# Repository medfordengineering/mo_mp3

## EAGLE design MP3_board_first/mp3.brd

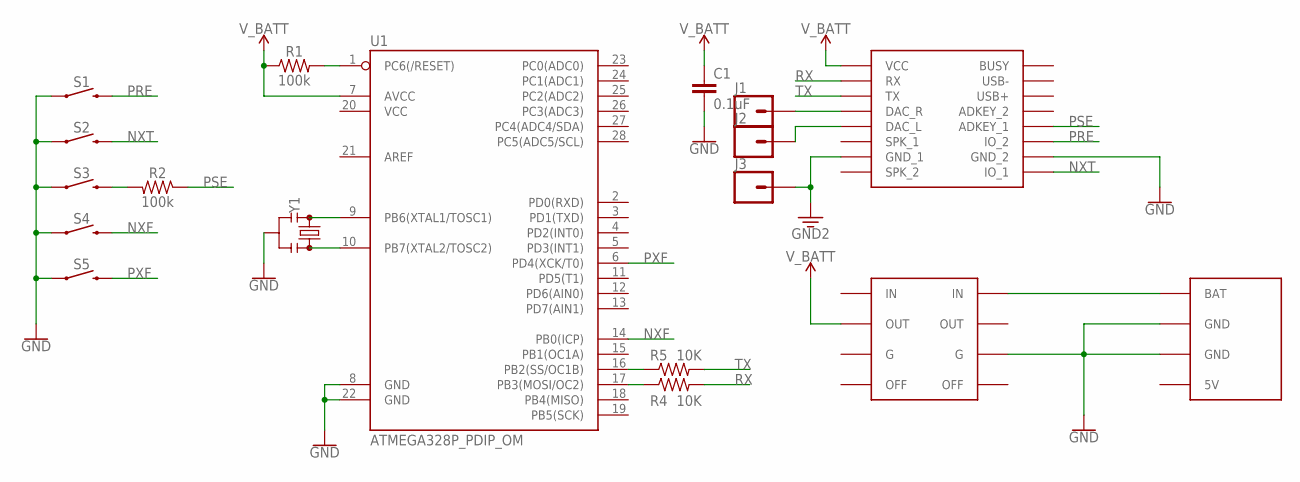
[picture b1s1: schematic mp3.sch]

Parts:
C1: 0.1uF; CAP-PTH-SMALL-KIT
J1, J2, J3: CONN_01PTH_NO_SILK_KIT; 1X01NS_KIT
R1, R2: 100k; AXIAL-0.3
R4, R5: 10K; AXIAL-0.3
S1, S2, S3, S4, S5: MOMENTARY-SWITCH-SPST-PTH-RIGHT-ANGLE; TACTILE_SWITCH_PTH_RIGHT_ANGLE
U1: ATMEGA328P_PDIP_OM; DIP28_OMILL
U$1: DFPLAYER
U$2: ADAFRUIT_SOFTPOWER
U$3: ADAFRUIT_CHARGER
Y1: RESONATOROM; RESONATOR-PTH-7.6X3.3-OM

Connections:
3.3V: J3.1, U$1.GND_1
GND: C1.2, S1.1, S2.1, S3.1, S4.1, S5.1, U1.8 (GND), U1.22 (GND), U$1.GND_2, U$2.P$2 (G), U$3.P$2 (GND), U$3.P$3 (GND), Y1.2
unnamed: U1.9 (PB6(XTAL1/TOSC1)), Y1.1
unnamed: U1.10 (PB7(XTAL2/TOSC2)), Y1.3
unnamed: R1.P$2 (2), U1.1 (PC6(/RESET))
unnamed: R5.P$1 (1), U1.17 (PB3(MOSI/OC2))
unnamed: R4.P$1 (1), U1.16 (PB2(SS/OC1B))
unnamed: R2.P$2 (2), S3.2
unnamed: U$2.P$4 (IN), U$3.P$1 (BAT)
unnamed: J1.1, U$1.DAC_R
unnamed: J2.1, U$1.DAC_L
NXF: S4.2, U1.14 (PB0(ICP))
NXT: S2.2, U$1.IO1 (IO_1)
PRE: S1.2, U$1.IO2 (IO_2)
PSE: R2.P$1 (1), U$1.ADKEY1 (ADKEY_1)
PXF: S5.2, U1.6 (PD4(XCK/T0))
RX: R5.P$2 (2), U$1.RX
TX: R4.P$2 (2), U$1.TX
V_BATT: C1.1, R1.P$1 (1), U1.7 (AVCC), U$1.VCC, U$2.P$6 (OUT)

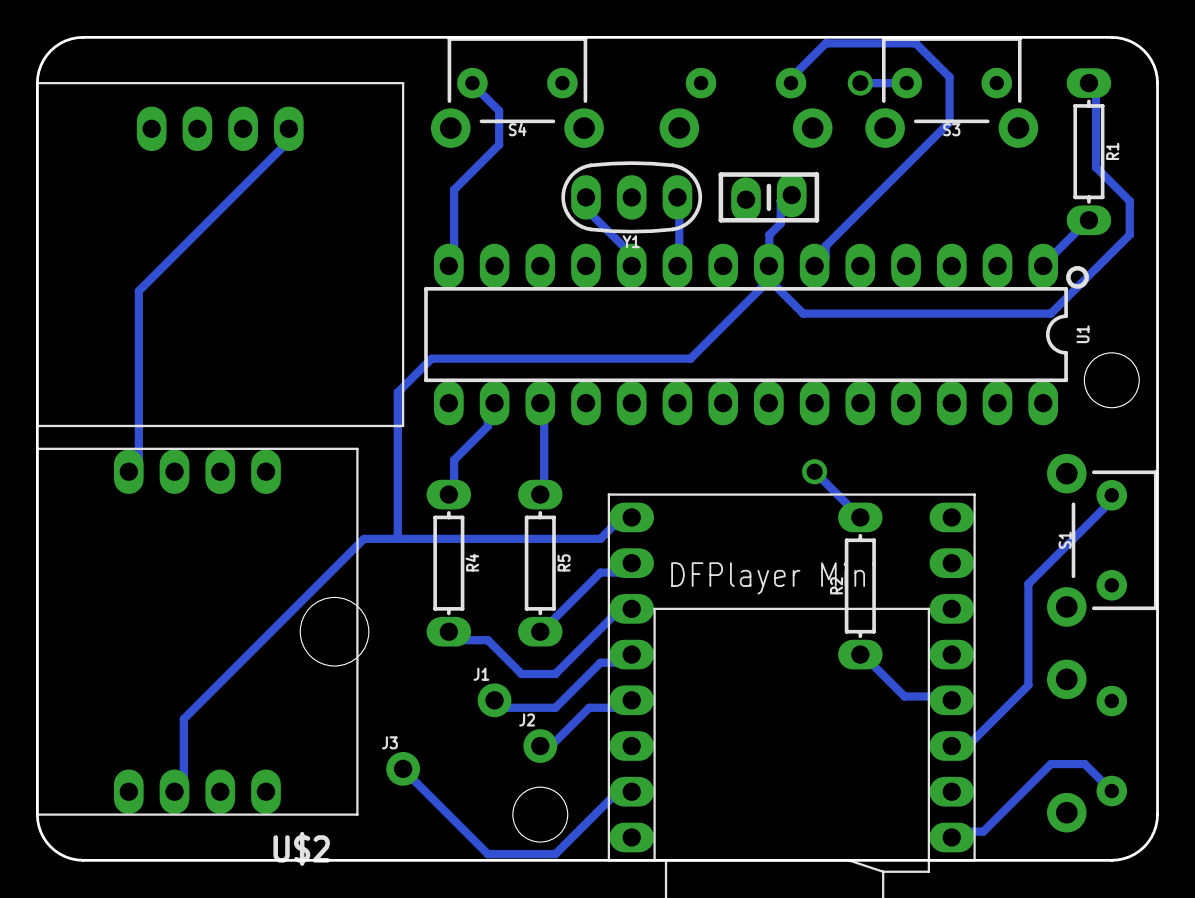
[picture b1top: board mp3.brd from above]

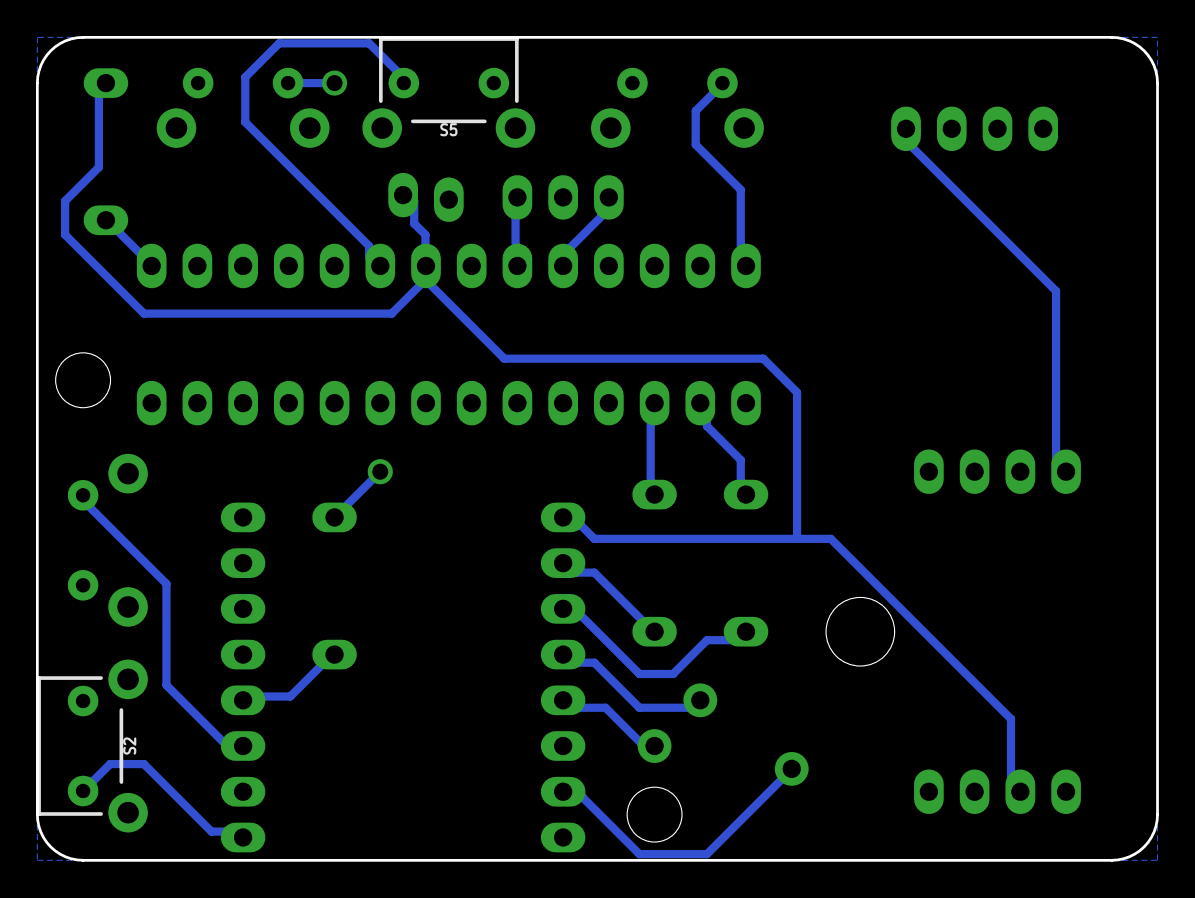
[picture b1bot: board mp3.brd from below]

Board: 2 copper layers, 62.2 x 45.7 mm, 18 parts (2 on the bottom side), 19 nets.

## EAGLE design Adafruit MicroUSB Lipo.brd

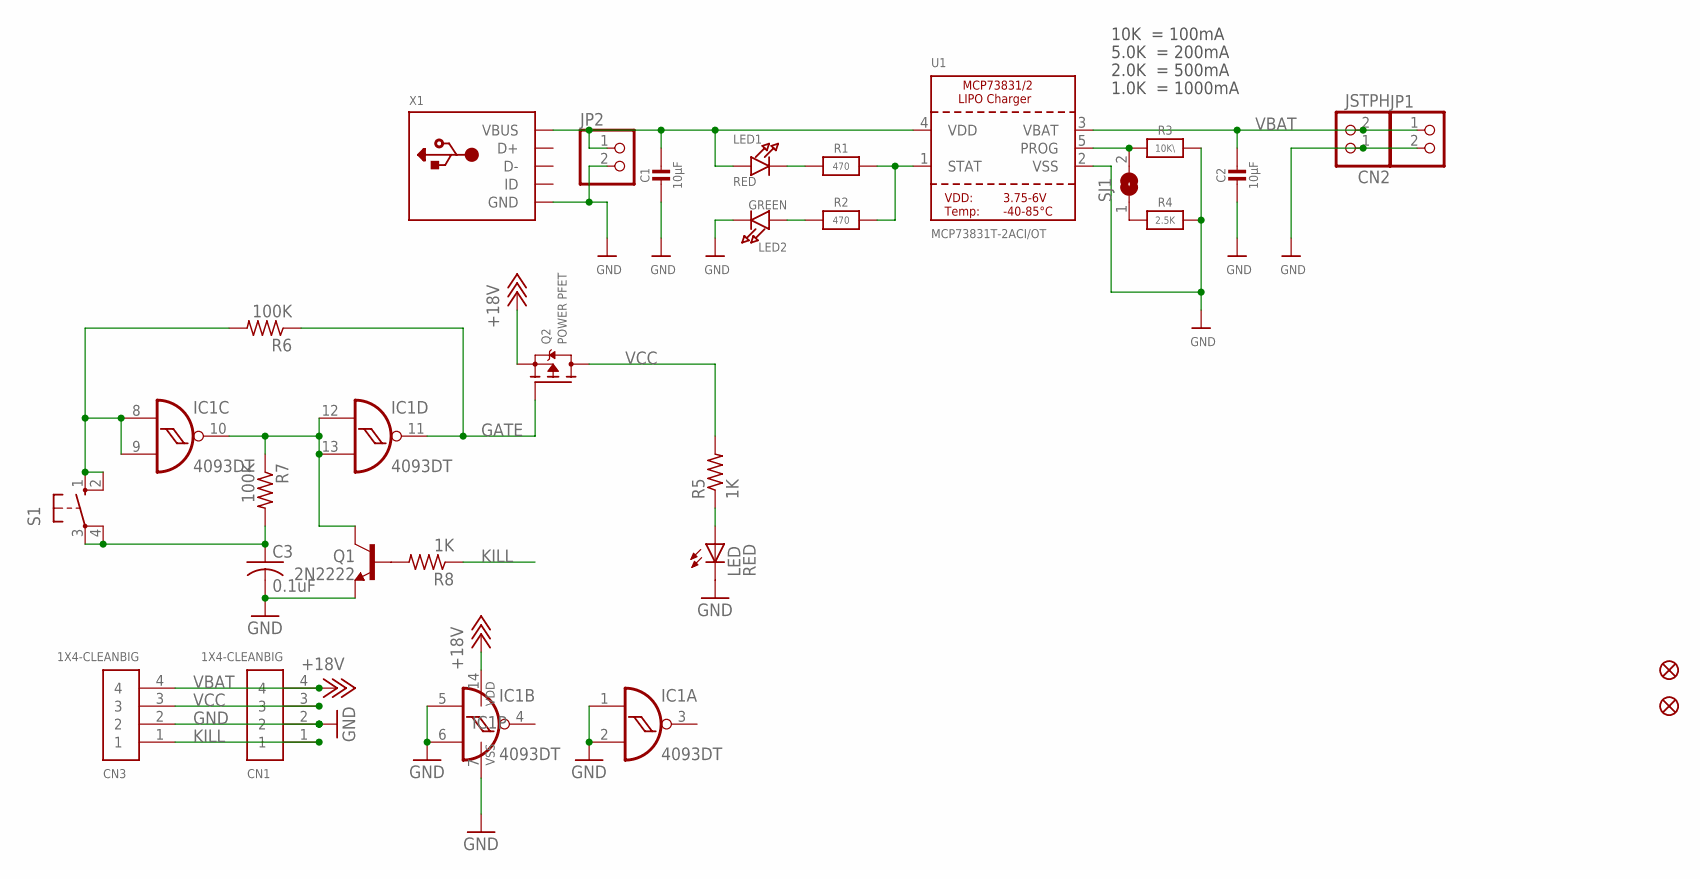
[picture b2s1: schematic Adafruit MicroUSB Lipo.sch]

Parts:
C1, C2: 10µF; 0805-NO
C3: 0.1uF; C0805
CN1, CN3: 1X4-CLEANBIG; 1X04-CLEANBIG
CN2: JSTPH; JSTPH2
FID1, FID2: FIDUCIAL""; FIDUCIAL_1MM
IC1: 4093DT; MC14093B-TSSOP14
JP1, JP2: HEADER-1X2ROUND; 1X02_ROUND
LED: RED; CHIP-LED0805
LED1: RED; CHIPLED_0805_NOOUTLINE
LED2: GREEN; CHIPLED_0805_NOOUTLINE
Q1: 2N2222; SOT23-BEC
Q2: POWER PFET; SOT23-WIDE
R1, R2: 470; 0805-NO
R3: 10K\; 0805-NO
R4: 2.5K; 0805-NO
R5, R8: 1K; R0805
R6, R7: 100K; R0805
S1: 40-XX-ROUND; B3F-40XX-ROUND
SJ1: SOLDERJUMPER; SOLDERJUMPER_ARROW_NOPASTE
U1: MCP73831T-2ACI/OT; SOT23-5
X1: USBMICRO_20329; 4UCONN_20329

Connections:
GATE: IC1.11 (O), Q2.1 (G), R6.1
GND: C1.2, C2.2, C3.2, CN1.2, CN2.1, CN3.2, IC1.1 (I0), IC1.2 (I1), IC1.5 (I0), IC1.6 (I1), IC1.7 (VSS), JP1.2, JP2.2, LED.C, LED2.C, Q1.E, R3.2, R4.2, U1.2 (VSS), X1.BASE@1 (GND), X1.BASE@2 (GND), X1.GND, X1.SPRT@1 (GND), X1.SPRT@2 (GND), X1.SPRT@3 (GND), X1.SPRT@4 (GND)
KILL: CN1.1, CN3.1, R8.1
unnamed: LED1.C, R1.1
unnamed: R1.2, R2.2, U1.1 (STAT)
unnamed: R4.1, SJ1.1
unnamed: IC1.10 (O), IC1.12 (I0), IC1.13 (I1), Q1.C, R7.1
unnamed: R3.1, SJ1.2, U1.5 (PROG)
unnamed: LED2.A, R2.1
unnamed: LED.A, R5.1
unnamed: C3.1, R7.2, S1.3, S1.4 (P1)
unnamed: IC1.8 (I0), IC1.9 (I1), R6.2, S1.1 (S), S1.2 (S1)
unnamed: Q1.B, R8.2
VBAT: C2.1, CN1.4, CN2.2, CN3.4, IC1.14 (VDD), JP1.1, Q2.2 (S), U1.3 (VBAT)
VCC: CN1.3, CN3.3, Q2.3 (D), R5.2
VDD: C1.1, JP2.1, LED1.A, U1.4 (VDD), X1.VBUS

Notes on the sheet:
10K = 100mA
5.0K = 200mA
2.0K = 500mA
1.0K = 1000mA

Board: 2 copper layers, 29 parts (1 on the bottom side), 16 nets, no tracks yet.

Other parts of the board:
U$13: ADAFRUIT_5MM

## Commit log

2019-01-18 First commit of board file
2019-01-25 first draft of board and code
2019-02-05 first soldered version of board
2019-02-06 Few small changes to board
2019-02-06 few more changes
2019-03-01 mostly done?

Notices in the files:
parts and their libraries:
microbuilder: This work is placed in the public domain, and may be freely used for commercial and non-commercial work with the following conditions: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
SparkFun-Switches: Licensing: Creative Commons ShareAlike 4.0 International - https://creativecommons.org/licenses/by-sa/4.0
